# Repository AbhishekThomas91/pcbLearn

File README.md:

# 555 Timer STEM Toy PCB

## Overview

This project is a beginner PCB designed in KiCad as part of a STEM electronics learning exercise.

The circuit is based on the popular NE555 timer IC and demonstrates the complete PCB design workflow, including schematic capture, footprint assignment, PCB layout, routing, and 3D visualization.

## Features

* NE555 timer based circuit
* Through-hole components
* Beginner-friendly PCB design
* Designed using KiCad
* Suitable for STEM and electronics learning

## Components

| Component | Value                  |
| --------- | ---------------------- |
| U1        | NE555 Timer IC         |
| R1        | 10 kΩ Resistor         |
| R2        | 1 kΩ Resistor          |
| C1        | Capacitor              |
| C2        | Electrolytic Capacitor |
| TP1       | Battery Input          |
| TP2       | Human Contact Terminal |
| TP3       | Buzzer Output          |

## Design Files

The repository contains:

* KiCad schematic files
* KiCad PCB layout files
* 3D PCB render
* Manufacturing files (Gerbers)

## Tools Used

* KiCad
* GitHub

## Learning Outcomes

Through this project I learned:

* Electronic schematic design
* Component footprint assignment
* PCB component placement
* PCB routing
* Design rule checking (DRC)
* 3D PCB visualization
* Preparing PCB files for manufacturing

## Screenshots

### 3D PCB View

Add the PCB render image here.

### PCB Layout

Add the PCB layout screenshot here.

### Schematic

Add the schematic screenshot here.

## Future Improvements

* Improve PCB compactness
* Add silkscreen labels
* Optimize routing
* Design a custom embedded hardware project
* Explore SMD component layouts

## License

This project is shared for educational and learning purposes.

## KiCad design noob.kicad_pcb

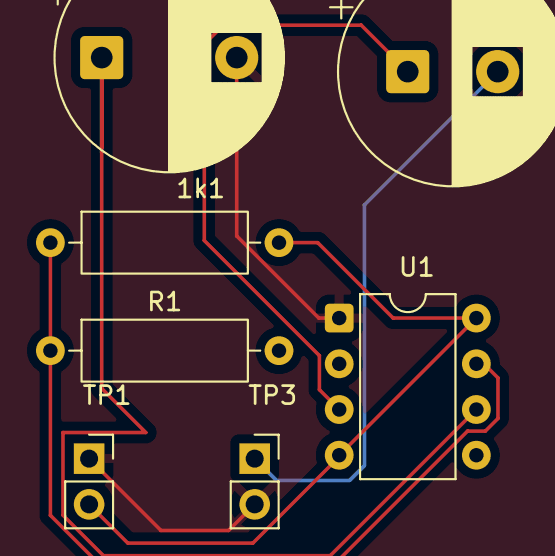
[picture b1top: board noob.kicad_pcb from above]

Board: 2 copper layers, 7 parts (0 on the bottom side), 6 nets.

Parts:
1k1: R; R_Axial_DIN0309_L9.0mm_D3.2mm_P12.70mm_Horizontal
C1: C; CP_Radial_D12.5mm_P7.50mm
C2: C_Polarized; CP_Radial_D12.5mm_P5.00mm
R1: 10k; R_Axial_DIN0309_L9.0mm_D3.2mm_P12.70mm_Horizontal
TP1: Battery; PinSocket_1x02_P2.54mm_Vertical
TP3: buzzer; PinSocket_1x02_P2.54mm_Vertical
U1: NE555P; DIP-8_W7.62mm

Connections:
/discharge: 1k1.1, R1.1, U1.7 (DIS)
/out: C2.1, U1.3 (Q)
/tr: C1.1, U1.2 (TR), U1.6 (THR)
GND: C1.2, TP1.1, TP3.2, U1.1 (GND)
unnamed: C2.2, TP3.1
VCC: 1k1.2, TP1.2, U1.4 (R), U1.8 (VCC)
